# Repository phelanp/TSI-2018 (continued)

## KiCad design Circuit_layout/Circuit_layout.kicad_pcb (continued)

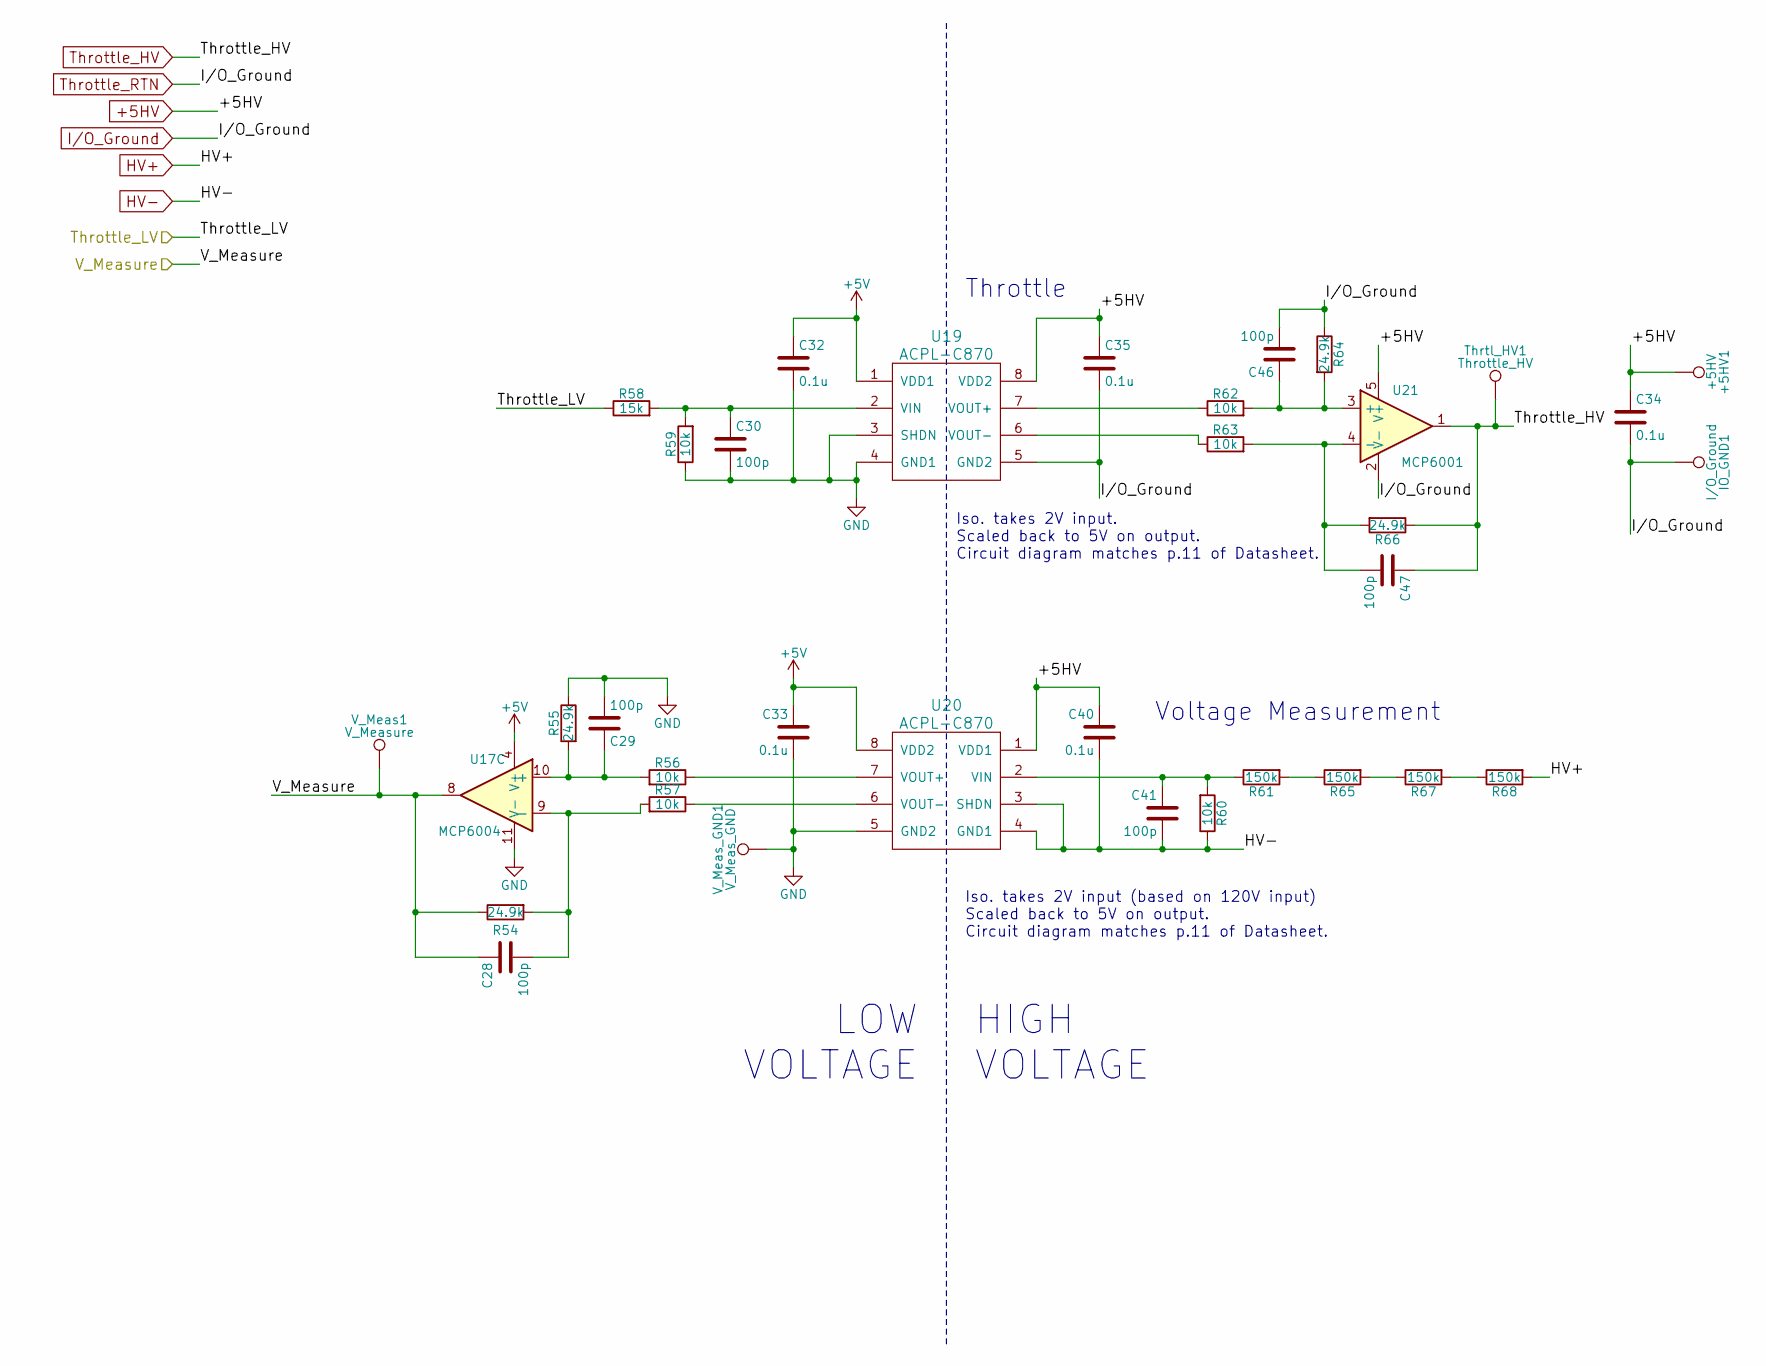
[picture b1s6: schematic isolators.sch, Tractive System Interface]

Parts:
+5HV1: +5HV; TSSOP-16-1EP_4.4x5mm_Pitch0.65mm
C28, C29, C30, C41, C46, C47: 100p; C_0805_HandSoldering; DigiKey P/N 399-1122-1-ND
C32, C33, C34, C35, C40: 0.1u; C_0805_HandSoldering; Digikey P/N 399-1168-1-ND
IO_GND1: I/O_Ground; Measurement_Point_Round-SMD-Pad_Big
R54, R55, R64, R66: 24.9k; R_0805_HandSoldering; DigiKey P/N P24.9KCCT-ND
R56, R57, R59, R60, R62, R63: 10k; R_0805_HandSoldering; DigiKey P/N P10.0KCCT-ND
R58: 15k; R_0805_HandSoldering; DigiKey P/N P24.9KCCT-ND
R61, R65, R67, R68: 150k; R_0805_HandSoldering; DigiKey P/N P150KCCT-ND
Thrtl_HV1: Throttle_HV; Measurement_Point_Round-SMD-Pad_Big
U17: MCP6004; SOIC-14_3.9x8.7mm_Pitch1.27mm; Digikey P/N MCP6004T-I/SLCT-ND
U19, U20: ACPL-C870; Iso_Diff_Amp_ACPL; Digikey P/N 516-2578-5-ND
U21: MCP6001; SOT-23-5_HandSoldering; DigiKey P/N MCP6001T-I/OTCT-ND
V_Meas1: V_Measure; Measurement_Point_Round-SMD-Pad_Big
V_Meas_GND1: V_Meas_GND; Measurement_Point_Square-SMD-Pad_Big

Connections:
+5HV: +5HV1.1, C34.1, C35.1, C40.1, U19.8 (VDD2), U20.1 (VDD1), U21.5 (V+); also elsewhere on the board
+5V: C32.1, C33.1, U17.4 (V+), U19.1 (VDD1), U20.8 (VDD2); also elsewhere on the board
/Throttle_LV: R58.1; also elsewhere on the board
/V_Measure: C28.1, R54.1, U17.8, V_Meas1.1; also elsewhere on the board
CH_GND: C29.2, C30.2, C32.2, C33.2, R55.1, R59.1, U17.11 (V-), U19.3 (SHDN), U19.4 (GND1), U20.5 (GND2), V_Meas_GND1.1; also elsewhere on the board
HV+: R68.2; also elsewhere on the board
HV-: C40.2, C41.2, R60.1, U20.3 (SHDN), U20.4 (GND1); also elsewhere on the board
I/O_Ground: C34.2, C35.2, C46.2, IO_GND1.1, R64.1, U19.5 (GND2), U21.2 (V-); also elsewhere on the board
unnamed: C28.2, R54.2, R57.2, U17.9 (-)
unnamed: C29.1, R55.2, R56.2, U17.10 (+)
unnamed: C30.1, R58.2, R59.2, U19.2 (VIN)
unnamed: C41.1, R60.2, R61.1, U20.2 (VIN)
unnamed: C46.1, R62.2, R64.2, U21.3 (+)
unnamed: C47.2, R63.2, R66.2, U21.4 (-)
unnamed: R56.1, U20.7 (VOUT+)
unnamed: R57.1, U20.6 (VOUT-)
unnamed: R61.2, R65.1
unnamed: R62.1, U19.7 (VOUT+)
unnamed: R63.1, U19.6 (VOUT-)
unnamed: R65.2, R67.1
unnamed: R67.2, R68.1
Throttle_HV: C47.1, R66.1, Thrtl_HV1.1, U21.1; also elsewhere on the board

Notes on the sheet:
Throttle
Voltage Measurement
HIGH VOLTAGE
LOW VOLTAGE
Iso. takes 2V input. Scaled back to 5V on output. Circuit diagram matches p.11 of Datasheet.
Iso. takes 2V input (based on 120V input) Scaled back to 5V on output. Circuit diagram matches p.11 of Datasheet.

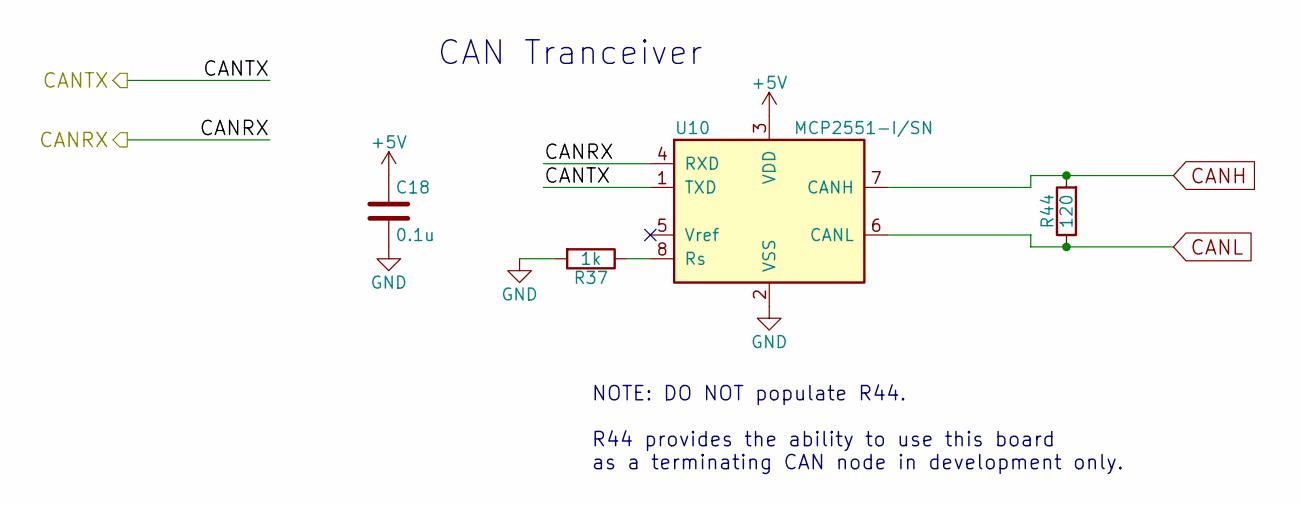
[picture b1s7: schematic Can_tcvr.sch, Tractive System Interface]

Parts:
C18: 0.1u; C_0805_HandSoldering; Digikey P/N 399-1168-1-ND
R37: 1k; R_0805_HandSoldering; DigiKey P/N P1.00KCCT-ND
R44: 120; R_0805_HandSoldering; DigiKey P/N 311-120CRCT-ND
U10: MCP2551-I/SN; SO-8; DigiKey P/N MCP2551-I/SN-ND

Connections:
+5V: C18.1, U10.3 (VDD); also elsewhere on the board
/CANRX: U10.4 (RXD); also elsewhere on the board
/CANTX: U10.1 (TXD); also elsewhere on the board
CANH: R44.2, U10.7 (CANH); also elsewhere on the board
CANL: R44.1, U10.6 (CANL); also elsewhere on the board
CH_GND: C18.2, R37.2, U10.2 (VSS); also elsewhere on the board
unnamed: R37.1, U10.8 (Rs)

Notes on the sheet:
CAN Tranceiver
NOTE: DO NOT populate R44. R44 provides the ability to use this board as a terminating CAN node in development only.

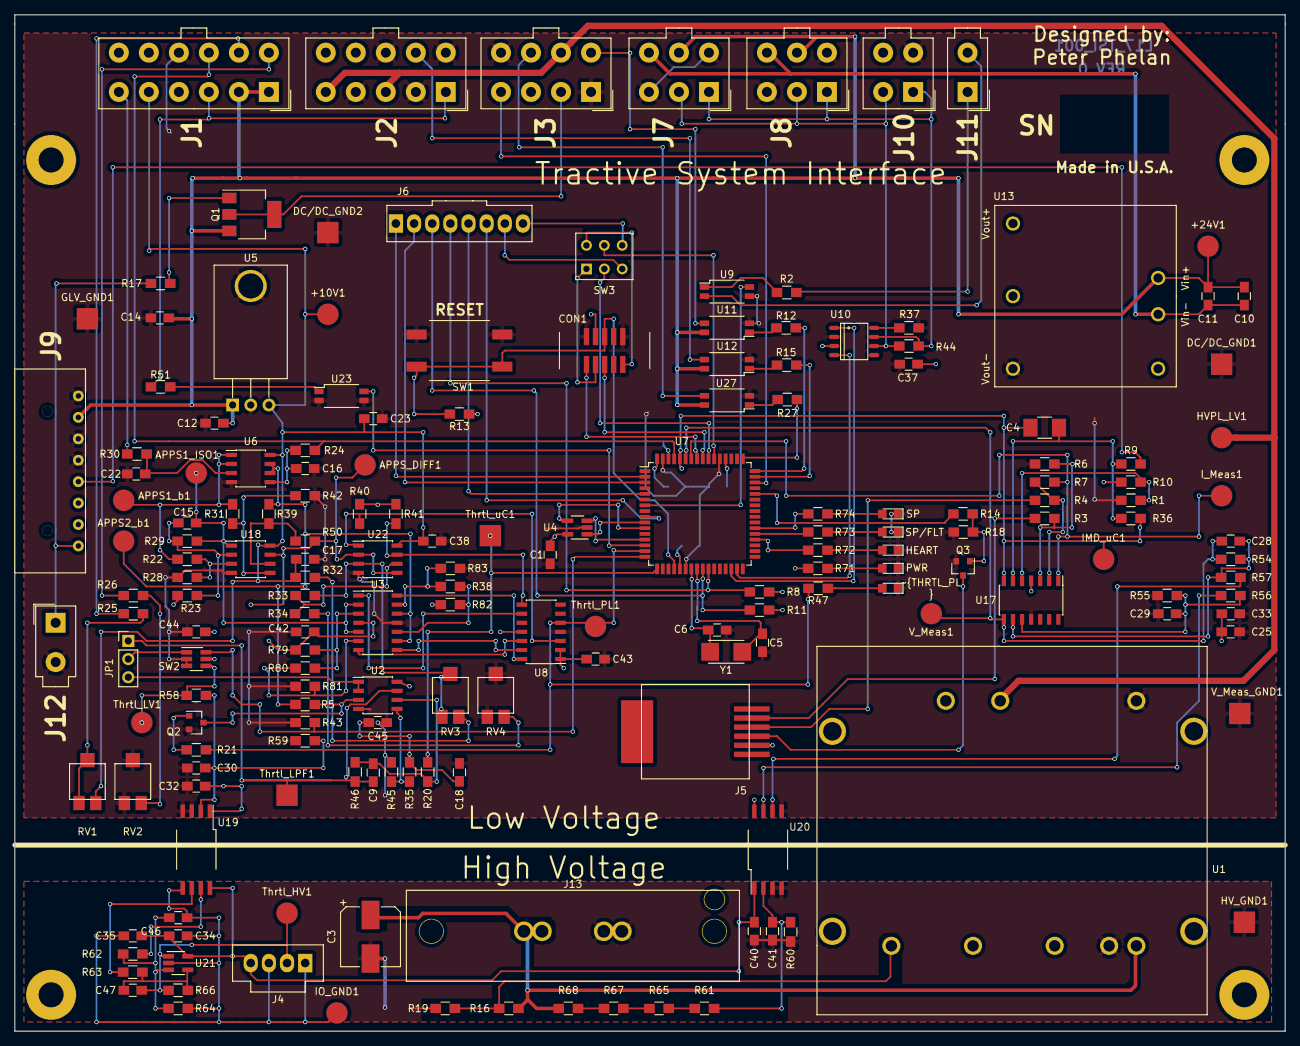
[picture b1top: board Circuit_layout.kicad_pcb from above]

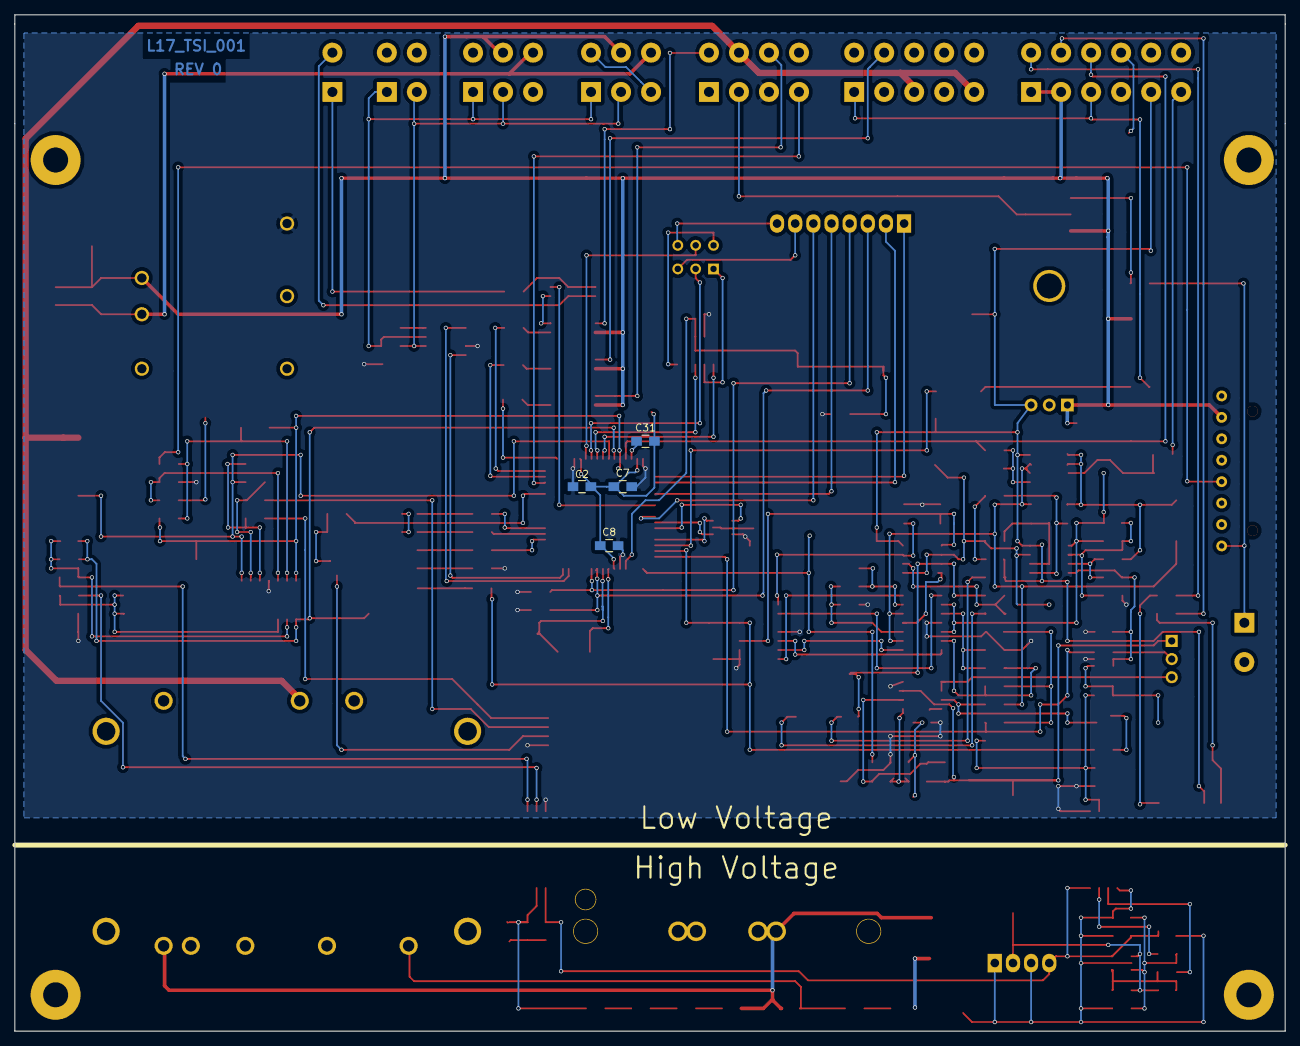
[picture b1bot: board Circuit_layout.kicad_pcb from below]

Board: 2 copper layers, 177.8 x 142.2 mm, 188 parts (4 on the bottom side), 133 nets.

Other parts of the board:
D5: ~Throttle_PL; LED_0805
R47: 1k; R_0805_HandSoldering

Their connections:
/Throttle_PL: R47.2; also elsewhere on the board
CH_GND: D5.1; also elsewhere on the board
unnamed: D5.2, R47.1

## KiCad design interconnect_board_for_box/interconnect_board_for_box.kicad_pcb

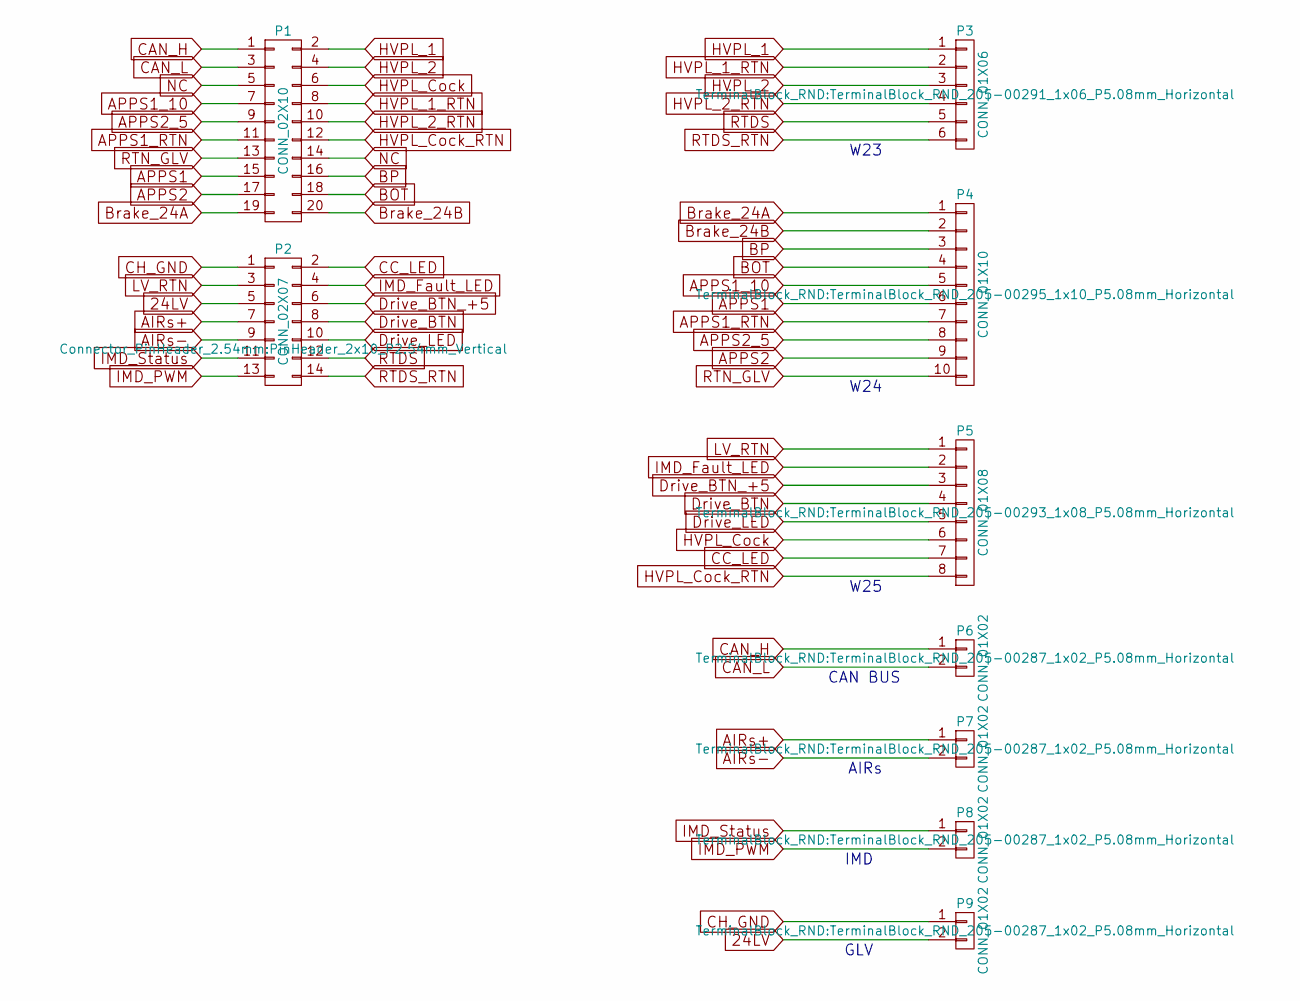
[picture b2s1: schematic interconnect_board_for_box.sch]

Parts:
P1: CONN_02X10; PinHeader_2x10_P2.54mm_Vertical
P2: CONN_02X07; PinHeader_2x07_P2.54mm_Vertical
P3: CONN_01X06; TerminalBlock_RND_205-00291_1x06_P5.08mm_Horizontal
P4: CONN_01X10; TerminalBlock_RND_205-00295_1x10_P5.08mm_Horizontal
P5: CONN_01X08; TerminalBlock_RND_205-00293_1x08_P5.08mm_Horizontal
P6, P7, P8, P9: CONN_01X02; TerminalBlock_RND_205-00287_1x02_P5.08mm_Horizontal

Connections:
24LV: P2.5, P9.2
AIRs+: P2.7, P7.1
AIRs-: P2.9, P7.2
APPS1: P1.15, P4.6
APPS1_10: P1.7, P4.5
APPS1_RTN: P1.11, P4.7
APPS2: P1.17, P4.9
APPS2_5: P1.9, P4.8
BOT: P1.18, P4.4
BP: P1.16, P4.3
Brake_24A: P1.19, P4.1
Brake_24B: P1.20, P4.2
CAN_H: P1.1, P6.1
CAN_L: P1.3, P6.2
CC_LED: P2.2, P5.7
CH_GND: P2.1, P9.1
Drive_BTN: P2.8, P5.4
Drive_BTN_+5: P2.6, P5.3
Drive_LED: P2.10, P5.5
HVPL_1: P1.2, P3.1
HVPL_1_RTN: P1.8, P3.2
HVPL_2: P1.4, P3.3
HVPL_2_RTN: P1.10, P3.4
HVPL_Cock: P1.6, P5.6
HVPL_Cock_RTN: P1.12, P5.8
IMD_Fault_LED: P2.4, P5.2
IMD_PWM: P2.13, P8.2
IMD_Status: P2.11, P8.1
LV_RTN: P2.3, P5.1
NC: P1.5, P1.14
RTDS: P2.12, P3.5
RTDS_RTN: P2.14, P3.6
RTN_GLV: P1.13, P4.10

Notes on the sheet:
W24
W23
W25
CAN BUS
AIRs
IMD
GLV

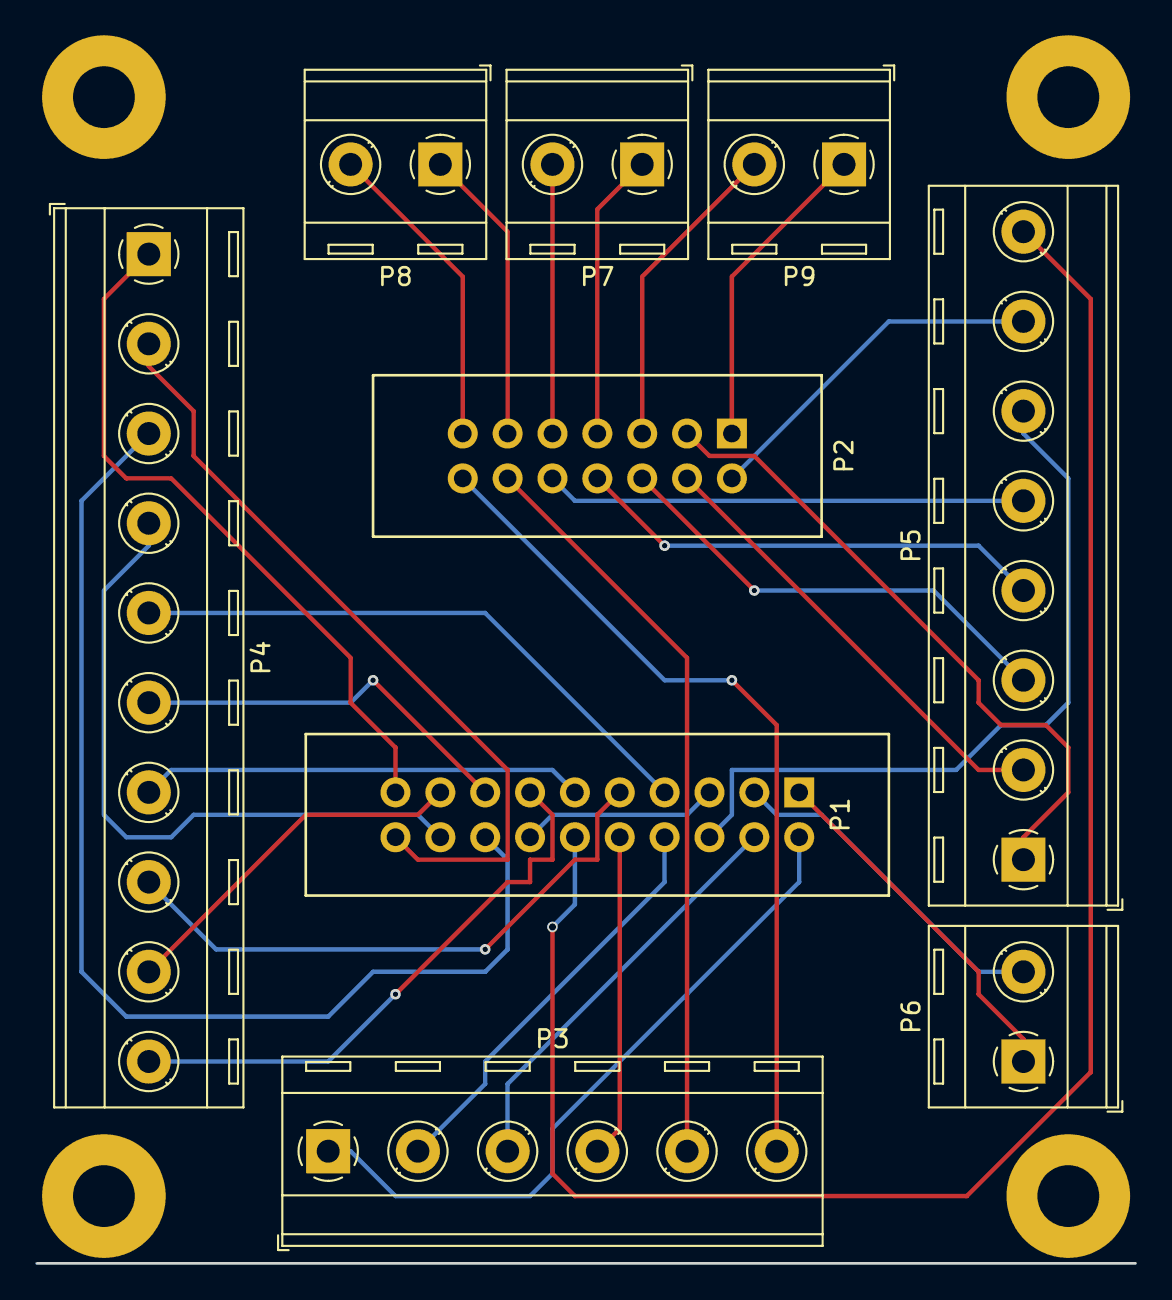
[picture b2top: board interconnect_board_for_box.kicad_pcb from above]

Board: 2 copper layers, 9 parts (0 on the bottom side), 33 nets.

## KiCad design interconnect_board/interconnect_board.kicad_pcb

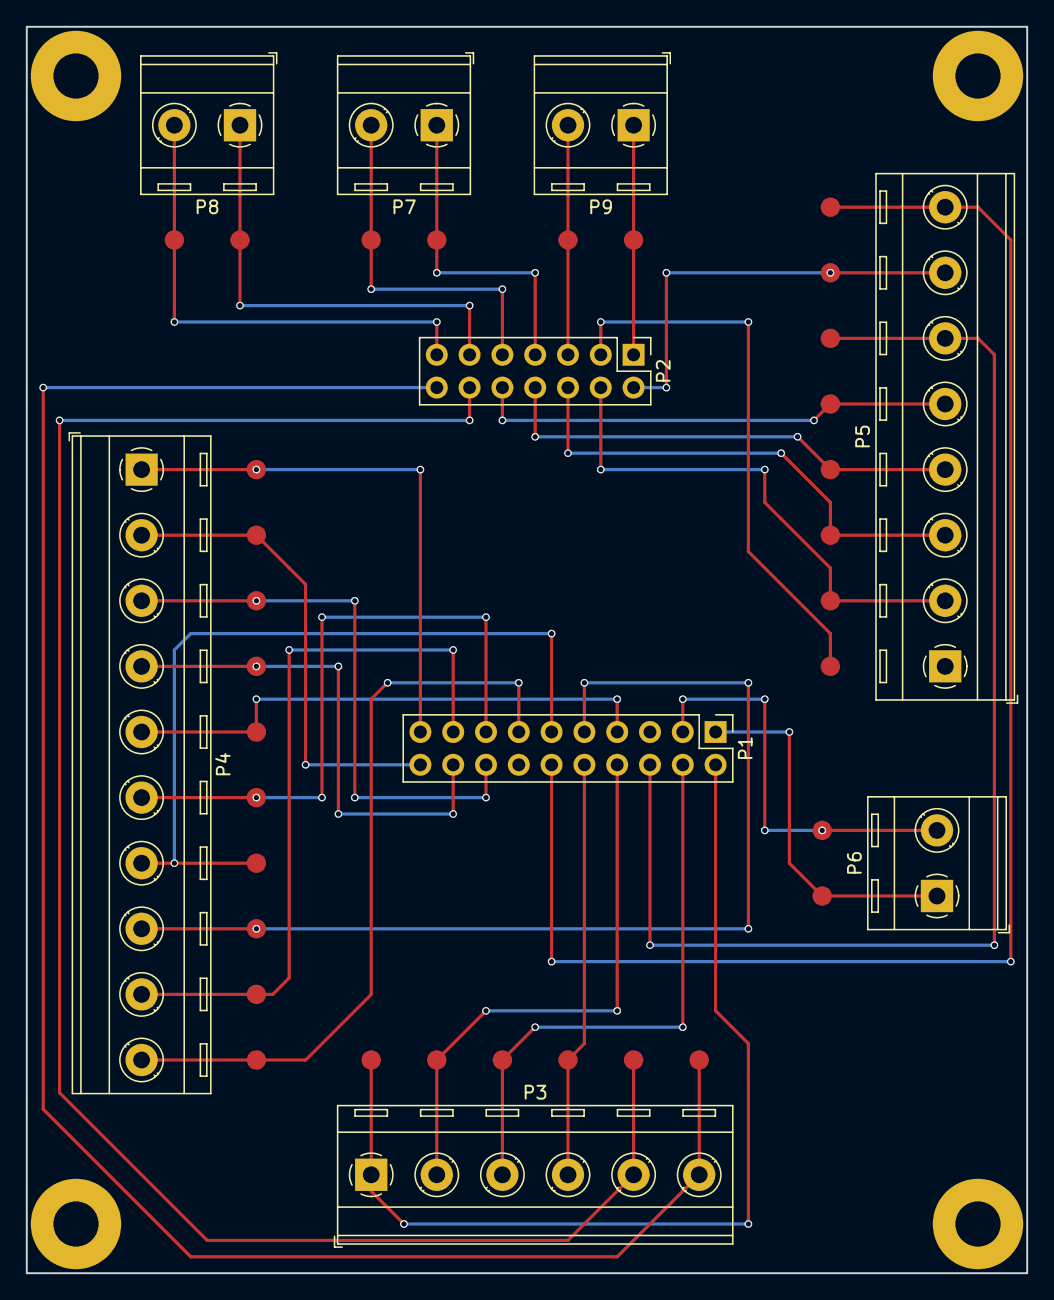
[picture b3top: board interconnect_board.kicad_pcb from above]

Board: 2 copper layers, 77.5 x 96.5 mm, 41 parts (0 on the bottom side), 33 nets.

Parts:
P1: CONN_02X10; PinHeader_2x10_P2.54mm_Vertical
P2: CONN_02X07; PinHeader_2x07_P2.54mm_Vertical
P3: CONN_01X06; TerminalBlock_RND_205-00291_1x06_P5.08mm_Horizontal
P4: CONN_01X10; TerminalBlock_RND_205-00295_1x10_P5.08mm_Horizontal
P5: CONN_01X08; TerminalBlock_RND_205-00293_1x08_P5.08mm_Horizontal
P6, P7, P8, P9: CONN_01X02; TerminalBlock_RND_205-00287_1x02_P5.08mm_Horizontal
W1: HVPL_1; Measurement_Point_Round-SMD-Pad_Small
W2, W17: HVPL_1_RTN; Measurement_Point_Round-SMD-Pad_Small
W3: RTDS; Measurement_Point_Round-SMD-Pad_Small
W4: Brake_24A; Measurement_Point_Round-SMD-Pad_Small
W5: BP; Measurement_Point_Round-SMD-Pad_Small
W6: APPS1_10; Measurement_Point_Round-SMD-Pad_Small
W7: APPS1_RTN; Measurement_Point_Round-SMD-Pad_Small
W8: APPS2; Measurement_Point_Round-SMD-Pad_Small
W9: LV_RTN; Measurement_Point_Round-SMD-Pad_Small
W10: Drive_BTN_+5; Measurement_Point_Round-SMD-Pad_Small
W11: Drive_LED; Measurement_Point_Round-SMD-Pad_Small
W12: CC_LED; Measurement_Point_Round-SMD-Pad_Small
W13: CAN_H; Measurement_Point_Round-SMD-Pad_Small
W14: AIRs+; Measurement_Point_Round-SMD-Pad_Small
W15: IMD_Status; Measurement_Point_Round-SMD-Pad_Small
W16: CH_GND; Measurement_Point_Round-SMD-Pad_Small
W18: HVPL_2_RTN; Measurement_Point_Round-SMD-Pad_Small
W19: RTDS_RTN; Measurement_Point_Round-SMD-Pad_Small
W20: Brake_24B; Measurement_Point_Round-SMD-Pad_Small
W21: BOT; Measurement_Point_Round-SMD-Pad_Small
W22: APPS1; Measurement_Point_Round-SMD-Pad_Small
W23: APPS2_5; Measurement_Point_Round-SMD-Pad_Small
W24: RTN_GLV; Measurement_Point_Round-SMD-Pad_Small
W25: IMD_Fault_LED; Measurement_Point_Round-SMD-Pad_Small
W26: Drive_BTN; Measurement_Point_Round-SMD-Pad_Small
W27: HVPL_Cock; Measurement_Point_Round-SMD-Pad_Small
W28: HVPL_Cock_RTN; Measurement_Point_Round-SMD-Pad_Small
W29: CAN_L; Measurement_Point_Round-SMD-Pad_Small
W30: AIRs-; Measurement_Point_Round-SMD-Pad_Small
W31: IMD_PWM; Measurement_Point_Round-SMD-Pad_Small
W32: 24LV; Measurement_Point_Round-SMD-Pad_Small

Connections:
24LV: P2.5, P9.2, W32.1
AIRs+: P2.7, P7.1, W14.1
AIRs-: P2.9, P7.2, W30.1
APPS1: P1.15, P4.6, W22.1
APPS1_10: P1.7, P4.5, W6.1
APPS1_RTN: P1.11, P4.7, W7.1
APPS2: P1.17, P4.9, W8.1
APPS2_5: P1.9, P4.8, W23.1
BOT: P1.18, P4.4, W21.1
BP: P1.16, P4.3, W5.1
Brake_24A: P1.19, P4.1, W4.1
Brake_24B: P1.20, P4.2, W20.1
CAN_H: P1.1, P6.1, W13.1
CAN_L: P1.3, P6.2, W29.1
CC_LED: P2.2, P5.7, W12.1
CH_GND: P2.1, P9.1, W16.1
Drive_BTN: P2.8, P5.4, W26.1
Drive_BTN_+5: P2.6, P5.3, W10.1
Drive_LED: P2.10, P5.5, W11.1
HVPL_1: P1.2, P3.1, W1.1
HVPL_1_RTN: P1.8, P3.2, W17.1
HVPL_2: P1.4, P3.3, W2.1
HVPL_2_RTN: P1.10, P3.4, W18.1
HVPL_Cock: P1.6, P5.6, W27.1
HVPL_Cock_RTN: P1.12, P5.8, W28.1
IMD_Fault_LED: P2.4, P5.2, W25.1
IMD_PWM: P2.13, P8.2, W31.1
IMD_Status: P2.11, P8.1, W15.1
LV_RTN: P2.3, P5.1, W9.1
NC: P1.5, P1.14
RTDS: P2.12, P3.5, W3.1
RTDS_RTN: P2.14, P3.6, W19.1
RTN_GLV: P1.13, P4.10, W24.1

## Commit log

2018-02-08 Added interconnect board
2018-02-08 Placed component labels on interconnect board
2018-02-08 Added old TSI layout
2018-02-09 Created smaller version of interconnect board for inside TSI box
2018-02-09 Completed errata changes
    Committing before annotation, footprint assignment, and board relayout for backup purposes
2018-02-09 Associated footprints and generated new netlist
2018-02-09 Backup before pcb relayout
2018-02-09 Pots connected, just need to fit regulator on
2018-02-09 Board 1.1 for review
2018-02-09 Updated R32 and R34
2018-02-13 Wider traces for DC/DC converter
2018-02-16 Finished internal wiring diagram
2018-02-16 updated wiring diagram
2018-02-16 created pdf of wiring diagram
2018-02-20 created new wiring diagram with proposed box changes, updated connectors on board
2018-02-27 Generated gerber and drill files for board ordering
2018-02-27 Cleaned up repo
2018-04-09 Schematic update
    Changed schematic to reflect board as assembeled
2018-04-10 Zipped current version
